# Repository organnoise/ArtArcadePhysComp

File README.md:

# Tools
Codebase for all Art Arcade projects

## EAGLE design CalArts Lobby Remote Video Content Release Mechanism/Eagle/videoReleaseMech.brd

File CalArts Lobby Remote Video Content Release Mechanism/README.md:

# CalArts Lobby Remote Video Content Release Mechanism

### openFramerworks
Video looper, controlled based on OSC messages

### ChucK 
Chuck code is for the Raspberry Pi, it handles OSC messages telling OF to change videos

### Arduino 
Arduino code handles the coin-op and sends serial info based on activity 

### Eagle
Schematic and board for hardware of project connecting coin-op to Arduino-micro and enable transistor control of coin-op to manage when coin-op is functional

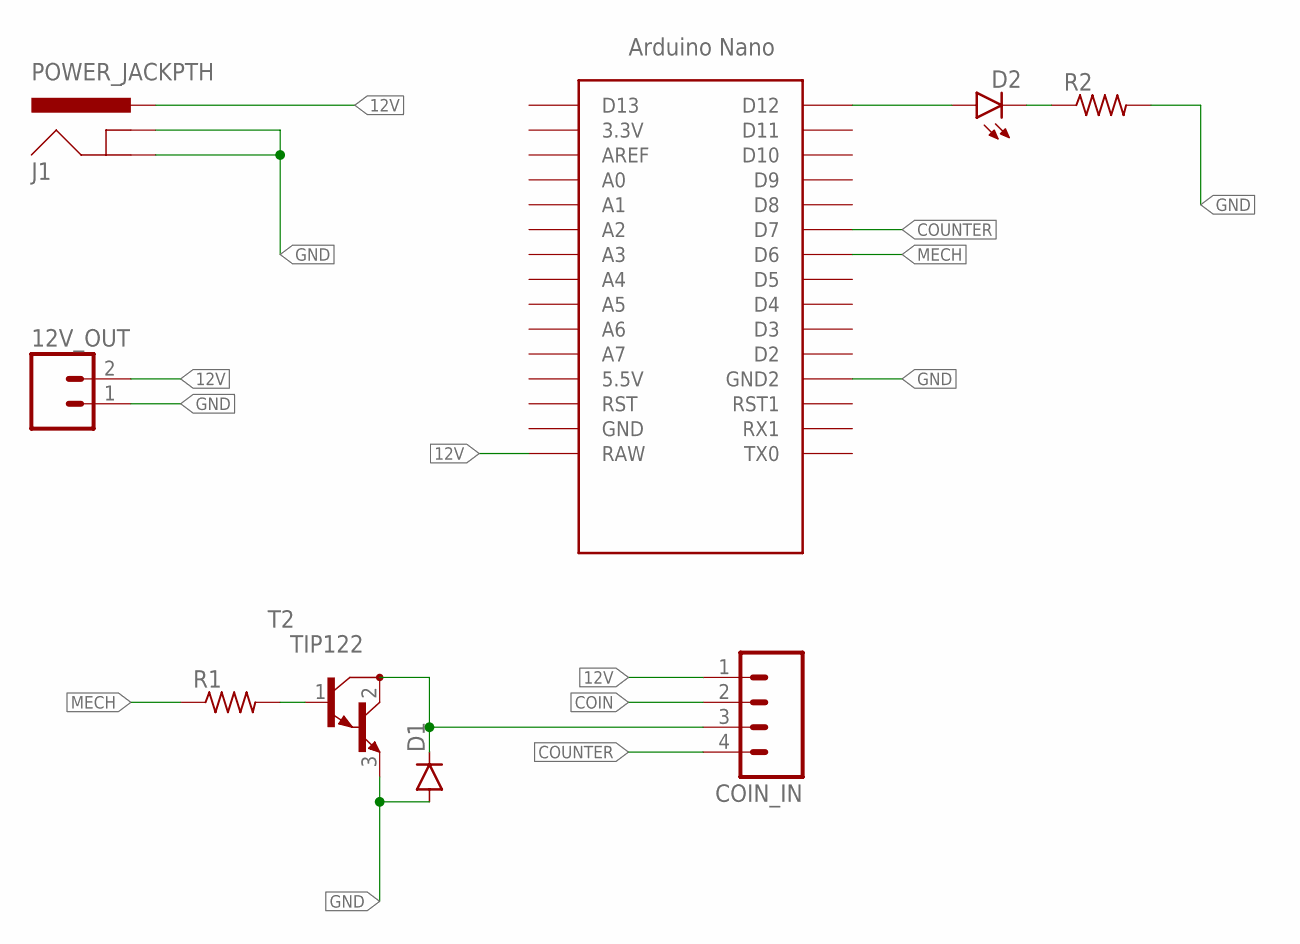
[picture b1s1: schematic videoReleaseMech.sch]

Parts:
12V_OUT: M02LOCK_LONGPADS; 1X02_LOCK_LONGPADS
COIN_IN: M041X04_NO_SILK; 1X04_NO_SILK
D1: DIODEPTH; DIODE-1N4001
D2: LED5MM
J1: POWER_JACKPTH; POWER_JACK_PTH
R1, R2: R-US_0411/3V; 0411V
T2: TIP122; TO220
U$1: NANO

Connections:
12V: 12V_OUT.2, COIN_IN.1, J1.PWR, U$1.RAW
COIN: COIN_IN.2
COUNTER: COIN_IN.4, U$1.D7
GND: 12V_OUT.1, D1.A, J1.GND, J1.GNDBREAK, R2.2, T2.3 (E), U$1.GND1 (GND2)
MECH: R1.1, U$1.D6
unnamed: COIN_IN.3, D1.C, T2.2 (C)
unnamed: R1.2, T2.1 (B)
unnamed: D2.K (C), R2.1
unnamed: D2.A, U$1.D12

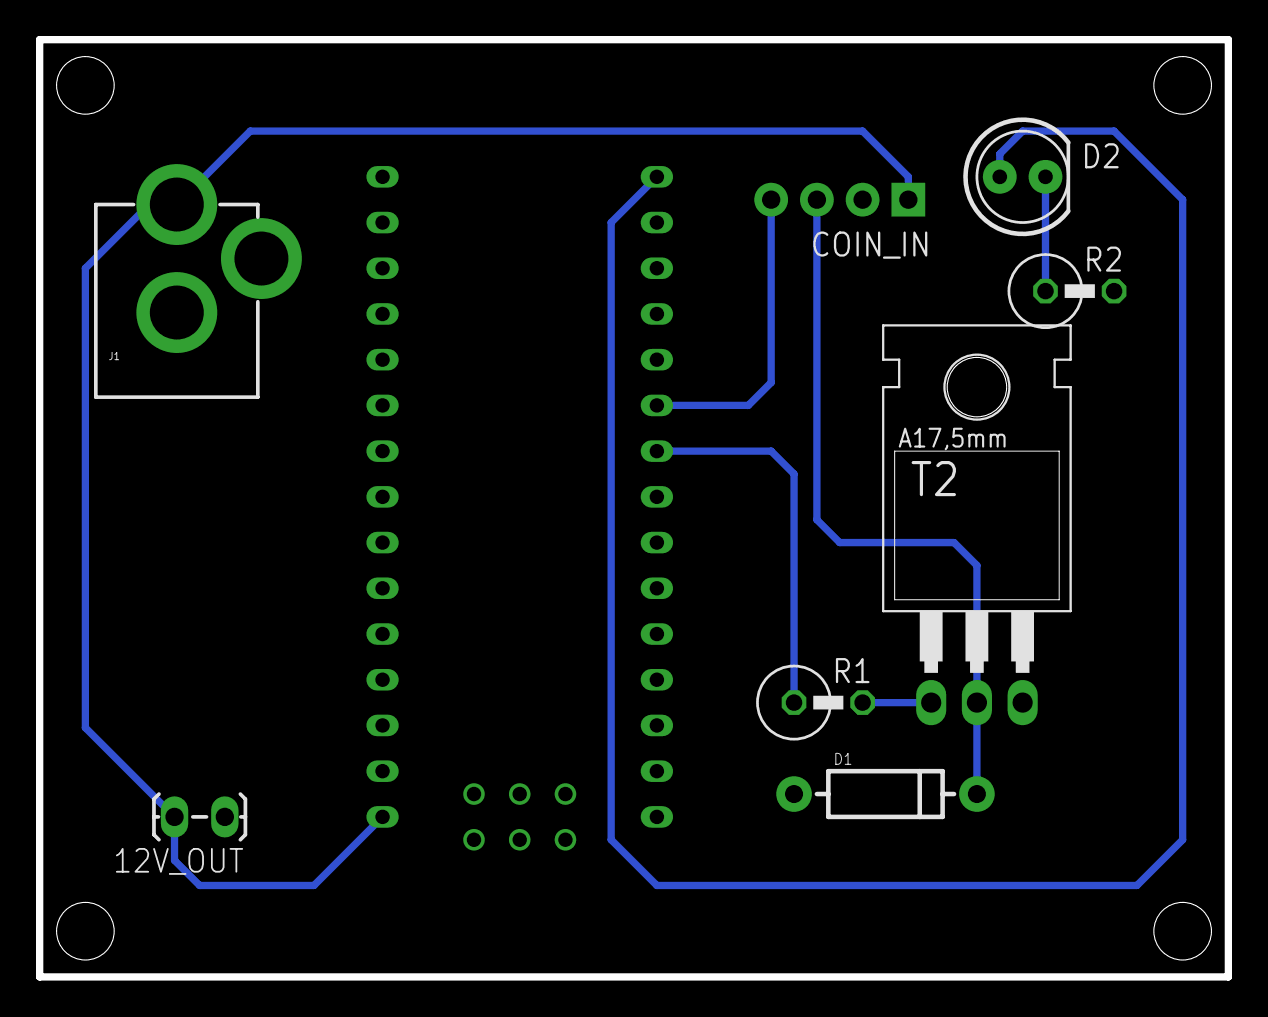
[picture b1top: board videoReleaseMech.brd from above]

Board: 2 copper layers, 66.0 x 52.1 mm, 9 parts (0 on the bottom side), 8 nets.

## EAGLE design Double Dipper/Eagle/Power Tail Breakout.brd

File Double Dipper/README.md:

# Double Dipper
### Arduino 
Arduino code handles the coin-op and controls relay for double-dipper motor accordingly.

### Eagle
Schematic and board for hardware of project connecting coin-op to Arduino-micro, enable transistor control of coin-op to manage when coin-op is functional, and toggle relay for power-tail. 

<p align="center">
  
</p>

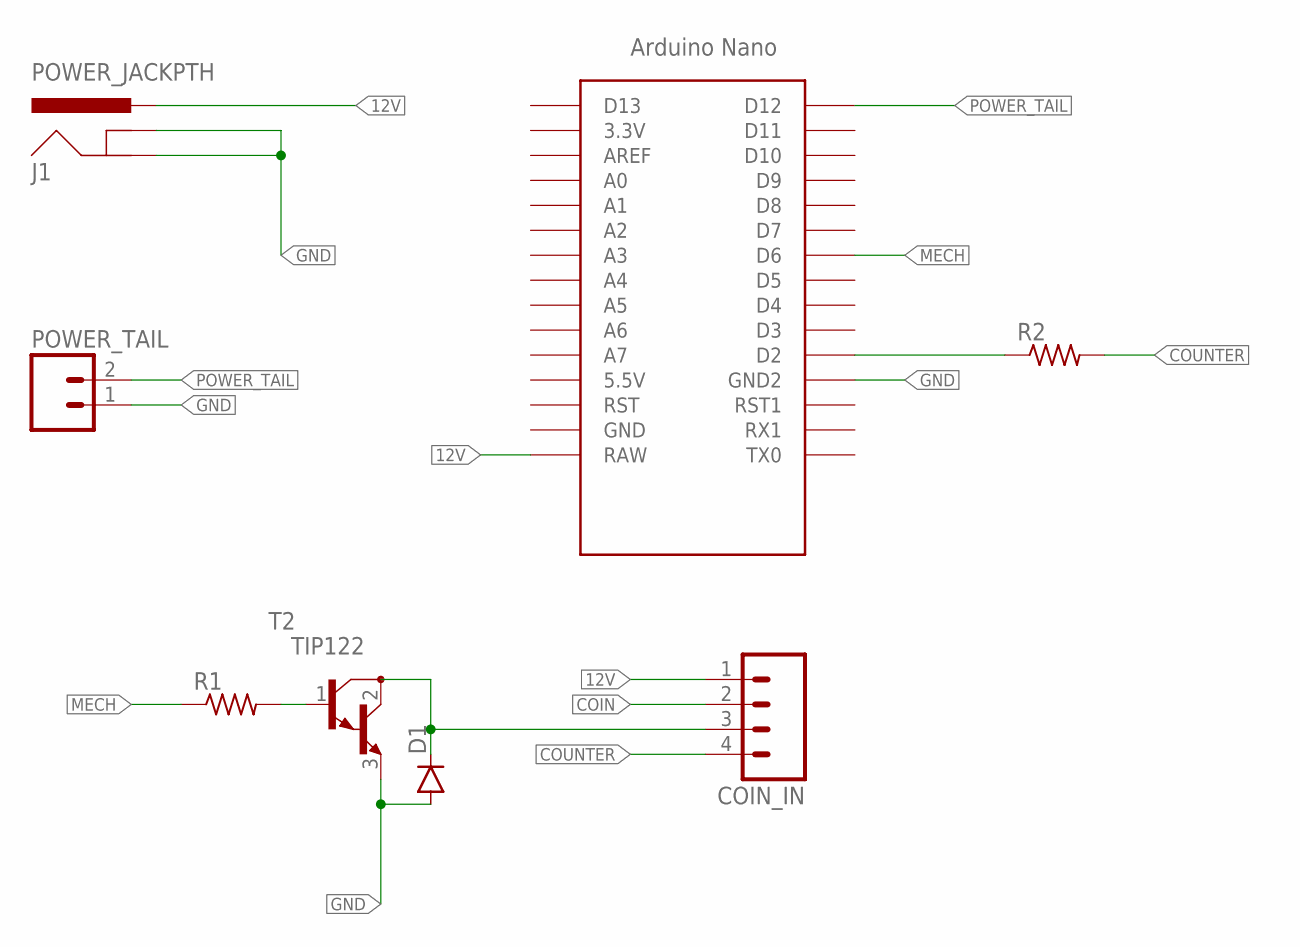
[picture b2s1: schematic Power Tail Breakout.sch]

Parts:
COIN_IN: M041X04_NO_SILK; 1X04_NO_SILK
D1: DIODEPTH; DIODE-1N4001
J1: POWER_JACKPTH; POWER_JACK_PTH
POWER_TAIL: M02LOCK_LONGPADS; 1X02_LOCK_LONGPADS
R1, R2: R-US_0411/3V; 0411V
T2: TIP122; TO220
U$1: NANO

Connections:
12V: COIN_IN.1, J1.PWR, U$1.RAW
COIN: COIN_IN.2
COUNTER: COIN_IN.4, R2.2
GND: D1.A, J1.GND, J1.GNDBREAK, POWER_TAIL.1, T2.3 (E), U$1.GND1 (GND2)
MECH: R1.1, U$1.D6
unnamed: COIN_IN.3, D1.C, T2.2 (C)
unnamed: R1.2, T2.1 (B)
unnamed: R2.1, U$1.D2
POWER_TAIL: POWER_TAIL.2, U$1.D12

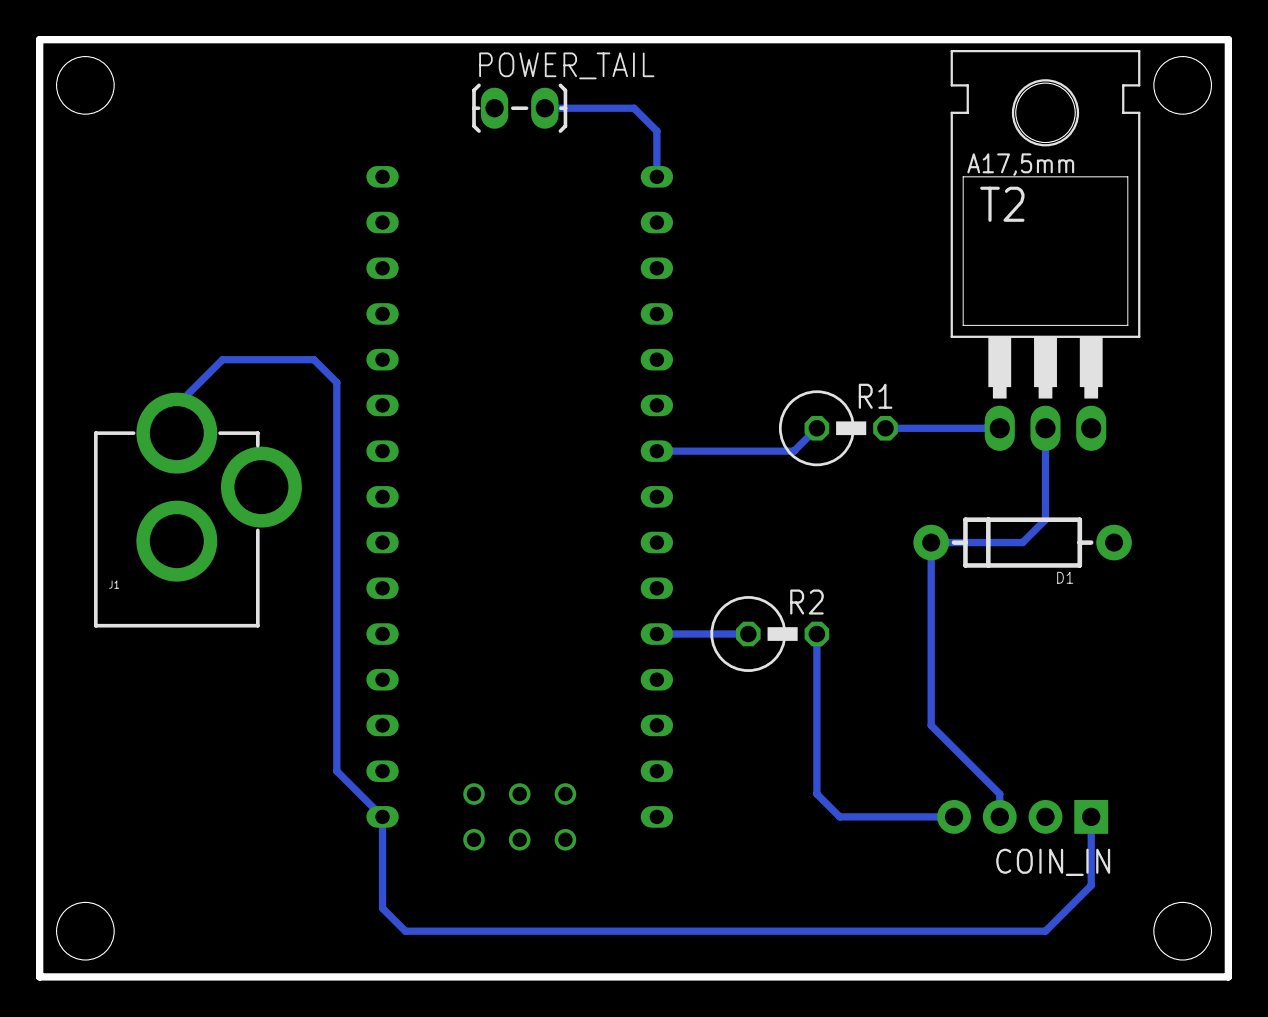
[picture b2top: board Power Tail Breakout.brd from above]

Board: 2 copper layers, 66.0 x 52.1 mm, 8 parts (0 on the bottom side), 8 nets.

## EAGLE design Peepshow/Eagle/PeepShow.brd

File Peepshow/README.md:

# Peepshow
### Arduino 
Arduino code handles the coin-op and sends serial info based on activity. Also controls stepper-driver based on button input 

### Eagle
Schematic and board for hardware of project connecting coin-op to Arduino-micro, enable transistor control of coin-op to manage when coin-op is functional, and communicate to easy-driver stepper hardware. 

<p align="center">
  
</p>

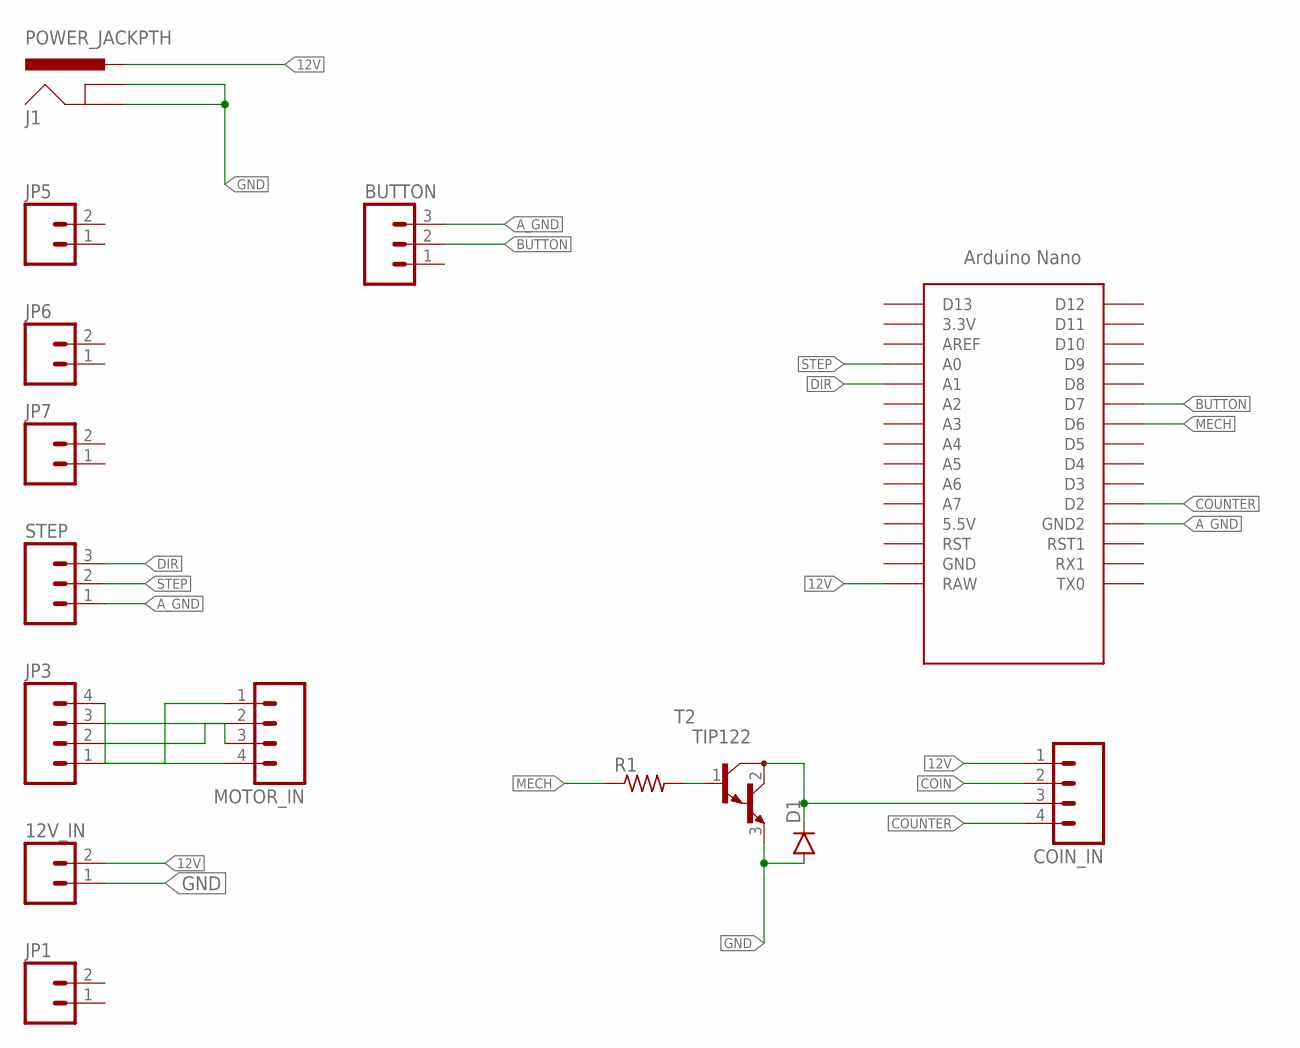
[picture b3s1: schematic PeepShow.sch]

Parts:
12V_IN: M021X02_NO_SILK; 1X02_NO_SILK
BUTTON: M031X03_NO_SILK; 1X03_NO_SILK
COIN_IN: M041X04_NO_SILK; 1X04_NO_SILK
D1: DIODEPTH; DIODE-1N4001
J1: POWER_JACKPTH; POWER_JACK_PTH
JP1, JP5, JP6, JP7: M021X02_NO_SILK; 1X02_NO_SILK
JP3: M041X04_NO_SILK; 1X04_NO_SILK
MOTOR_IN: M041X04_NO_SILK; 1X04_NO_SILK
R1: R-US_0411/3V; 0411V
STEP: M031X03_NO_SILK; 1X03_NO_SILK
T2: TIP122; TO220
U$1: NANO

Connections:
12V: 12V_IN.2, COIN_IN.1, J1.PWR, U$1.RAW
A_GND: BUTTON.3, STEP.1, U$1.GND1 (GND2)
BUTTON: BUTTON.2, U$1.D7
COIN: COIN_IN.2
COUNTER: COIN_IN.4, U$1.D2
DIR: STEP.3, U$1.A1
GND: 12V_IN.1, D1.A, J1.GND, J1.GNDBREAK, T2.3 (E)
MECH: R1.1, U$1.D6
unnamed: COIN_IN.3, D1.C, T2.2 (C)
unnamed: R1.2, T2.1 (B)
unnamed: JP3.1, MOTOR_IN.1
unnamed: JP3.2, MOTOR_IN.2
unnamed: JP3.3, MOTOR_IN.3
unnamed: JP3.4, MOTOR_IN.4
STEP: STEP.2, U$1.A0

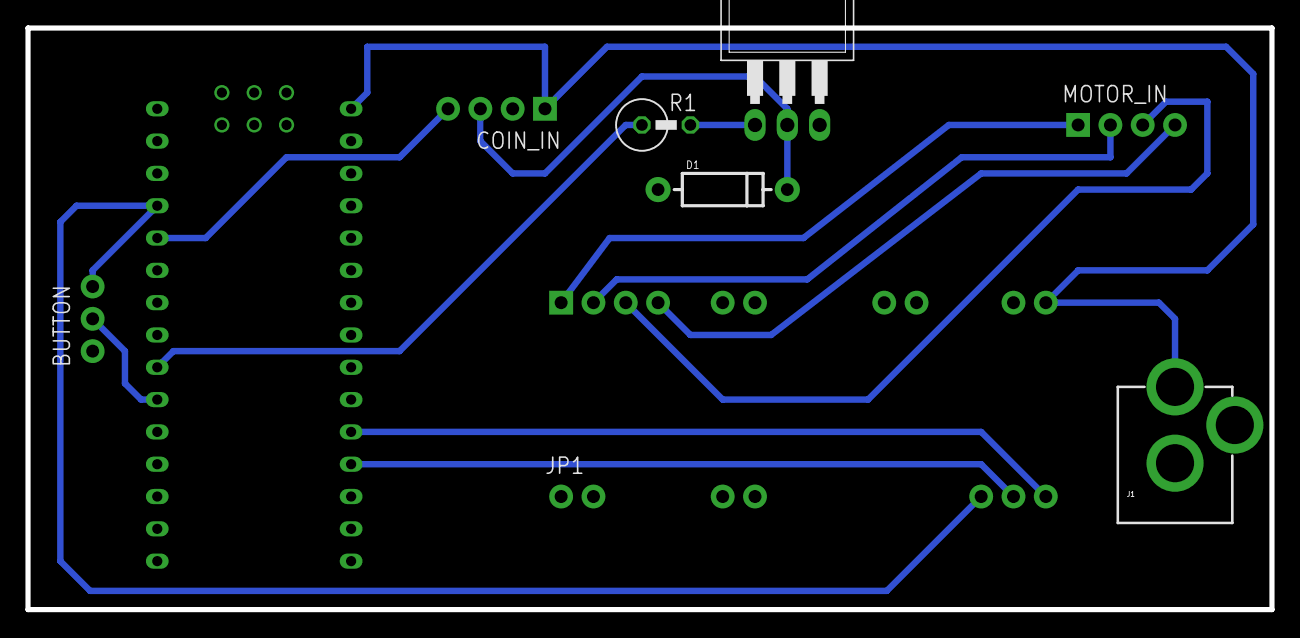
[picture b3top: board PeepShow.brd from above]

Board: 2 copper layers, 97.8 x 45.7 mm, 15 parts (0 on the bottom side), 14 nets.

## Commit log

2017-08-14 content
2017-08-14 ana wheel

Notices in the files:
parts and their libraries:
SparkFun-Connectors: Licensing: Creative Commons ShareAlike 4.0 International - https://creativecommons.org/licenses/by-sa/4.0
